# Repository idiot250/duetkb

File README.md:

# duetkb

**An open-source split stenography keyboard.**

duetkb is a DIY split stenography keyboard designed for fast, chord-based text input. It uses a compact two-piece layout, allowing both hands to operate independently while remaining connected to a single host computer.

i built this project for the idea of making dedicated stenographic hardware accessible, affordable, and customizable.

The first hardware revision is currently being designed. PCB design and firmware development are ongoing.

## Features

- Split keyboard architecture with independent left and right halves.
- 23-key stenographic layout.
- Wired USB-C connection to the host computer.
- Inter-half communication through a physical cable.
- ESP32-based hardware architecture.
- Designed for integration with [Plover](https://www.openstenoproject.org/plover/).
- Open-source hardware and firmware.

## Hardware

the keyboard is designed around two separate PCBs, one for each hand. it uses a row-and-column switch matrix with individual diodes to support simultaneous key presses and prevent unwanted electrical interactions.

| component | function |
|---|---|
| Microcontroller | ESP32 |
| Key switches | Mechanical switches |
| Diodes | Individual switch-matrix diodes |
| Host connection | USB-C |
| Inter-half connection | Wired |
| Layout | 23-key stenographic |

## repo structure

```text
duetkb/
├── hardware/
│   ├── left/
│   │   └── KiCad project files
│   └── right/
│       └── KiCad project files
├── firmware/
│   └── ESP-IDF project
├── JOURNAL.md
└── README.md
```

*Directory structure may change as development progresses.*

## Firmware

Firmware is being developed using **ESP-IDF**.

The intended firmware will handle:

- Switch matrix scanning.
- Simultaneous keypress detection.
- Communication between keyboard halves.
- Stenographic chord processing.
- USB HID output for compatibility with host computers and Plover.

## Software Compatibility

duetkb is intended to work with [Plover](https://www.openstenoproject.org/plover/), an open-source stenography engine.

The eventual goal is to translate simultaneous key combinations into stenographic input that Plover can interpret using a supported stenography dictionary and theory.

## Development

The hardware is designed in [KiCad](https://www.kicad.org/), while firmware development uses the ESP-IDF framework.

To work on the firmware, install ESP-IDF and its required toolchain.

```bash
git clone https://github.com/kurone741/duetkb.git
cd duetkb
```

Firmware build and flashing instructions will be added once the initial firmware implementation is ready.

## Roadmap

- [x] Establish project architecture.
- [x] Select initial hardware components.
- [x] Design left and right schematics.
- [x] Assign PCB footprints.
- [ ] Complete PCB component placement.
- [ ] Route both PCBs.
- [ ] Run PCB design-rule checks.
- [ ] Generate manufacturing files.
- [ ] Assemble hardware.
- [ ] Implement switch matrix scanning.
- [ ] Implement inter-half communication.
- [ ] Implement stenographic input processing.
- [ ] Test Plover compatibility.

## License

Licensing information will be added before the first public hardware and firmware release.

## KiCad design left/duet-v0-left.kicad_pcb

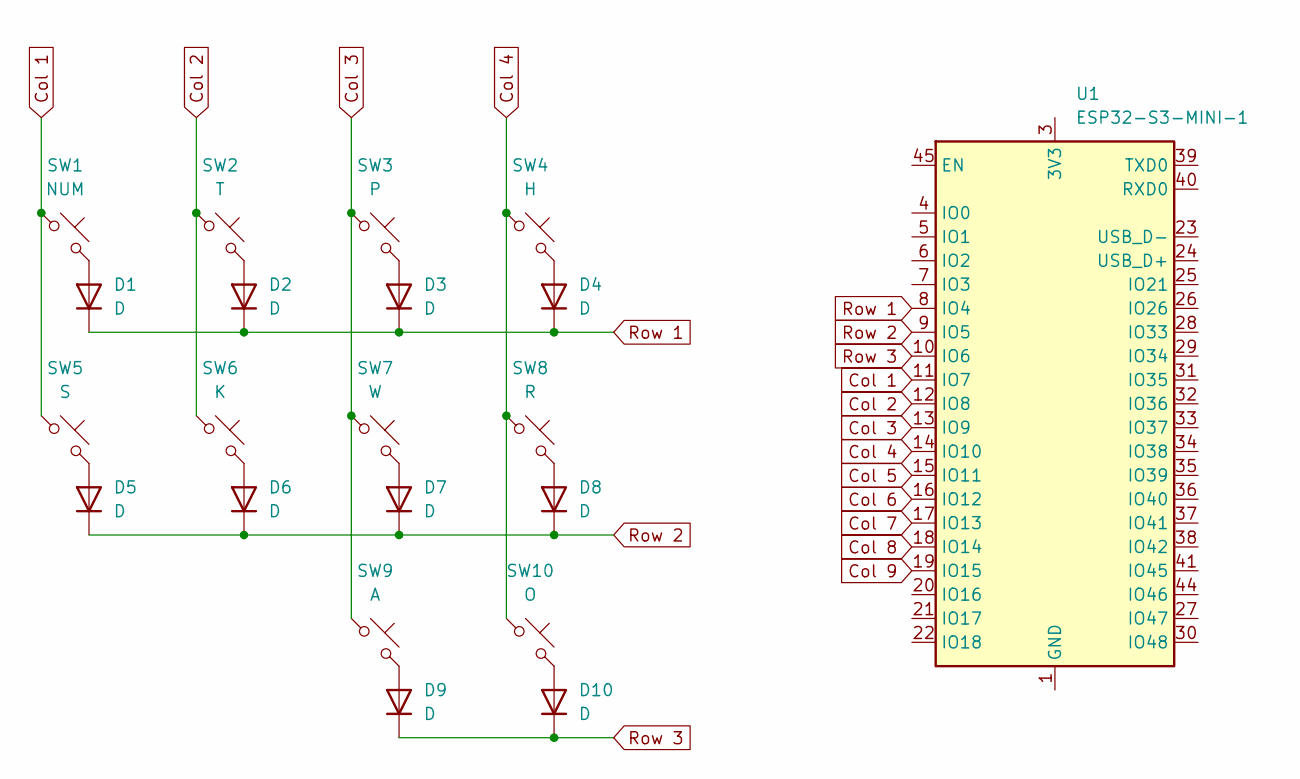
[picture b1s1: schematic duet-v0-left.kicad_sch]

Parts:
D1, D2, D3, D4, D5, D6, D7, D8, D9, D10: D; D_SOD-123
SW1: NUM; SW_Cherry_MX_1.00u_PCB
SW2: T; SW_Cherry_MX_1.00u_PCB
SW3: P; SW_Cherry_MX_1.00u_PCB
SW4: H; SW_Cherry_MX_1.00u_PCB
SW5: S; SW_Cherry_MX_1.00u_PCB
SW6: K; SW_Cherry_MX_1.00u_PCB
SW7: W; SW_Cherry_MX_1.00u_PCB
SW8: R; SW_Cherry_MX_1.00u_PCB
SW9: A; SW_Cherry_MX_1.00u_PCB
SW10: O; SW_Cherry_MX_1.00u_PCB
U1: ESP32-S3-MINI-1; ESP32-S2-MINI-1

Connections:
Col 1: SW1.1, SW5.1, U1.11 (IO7)
Col 2: SW2.1, SW6.1, U1.12 (IO8)
Col 3: SW3.1, SW7.1, SW9.1, U1.13 (IO9)
Col 4: SW4.1, SW8.1, SW10.1, U1.14 (IO10)
Col 5: U1.15 (IO11)
Col 6: U1.16 (IO12)
Col 7: U1.17 (IO13)
Col 8: U1.18 (IO14)
Col 9: U1.19 (IO15)
unnamed: D1.2 (A), SW1.2
unnamed: D2.2 (A), SW2.2
unnamed: D3.2 (A), SW3.2
unnamed: D4.2 (A), SW4.2
unnamed: D5.2 (A), SW5.2
unnamed: D6.2 (A), SW6.2
unnamed: D7.2 (A), SW7.2
unnamed: D8.2 (A), SW8.2
unnamed: D9.2 (A), SW9.2
unnamed: D10.2 (A), SW10.2
unnamed: U1.1 (GND), U1.2 (GND), U1.42 (GND), U1.43 (GND), U1.46 (GND), U1.47 (GND), U1.48 (GND), U1.49 (GND), U1.50 (GND), U1.51 (GND), U1.52 (GND), U1.53 (GND), U1.54 (GND), U1.55 (GND), U1.56 (GND), U1.57 (GND), U1.58 (GND), U1.59 (GND), U1.60 (GND), U1.61 (GND), U1.62 (GND), U1.63 (GND), U1.64 (GND), U1.65 (GND)
Row 1: D1.1 (K), D2.1 (K), D3.1 (K), D4.1 (K), U1.8 (IO4)
Row 2: D5.1 (K), D6.1 (K), D7.1 (K), D8.1 (K), U1.9 (IO5)
Row 3: D9.1 (K), D10.1 (K), U1.10 (IO6)

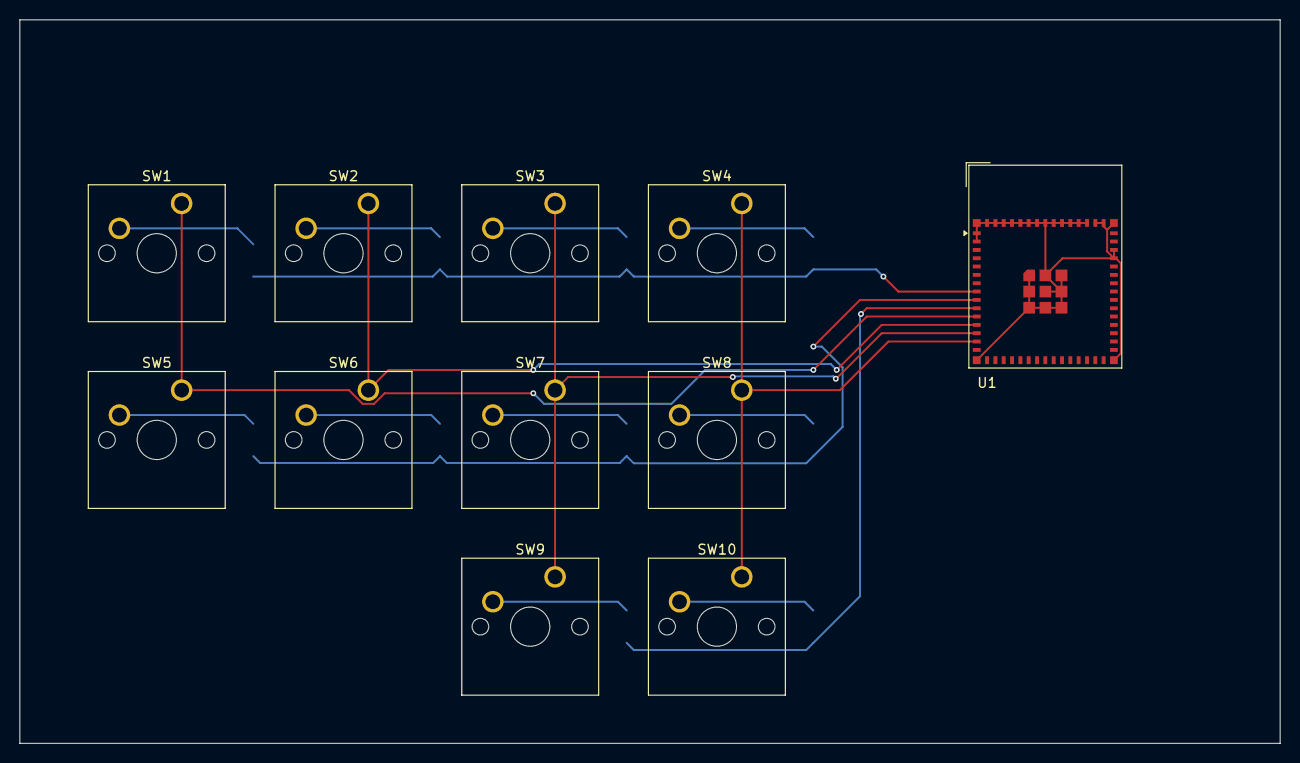
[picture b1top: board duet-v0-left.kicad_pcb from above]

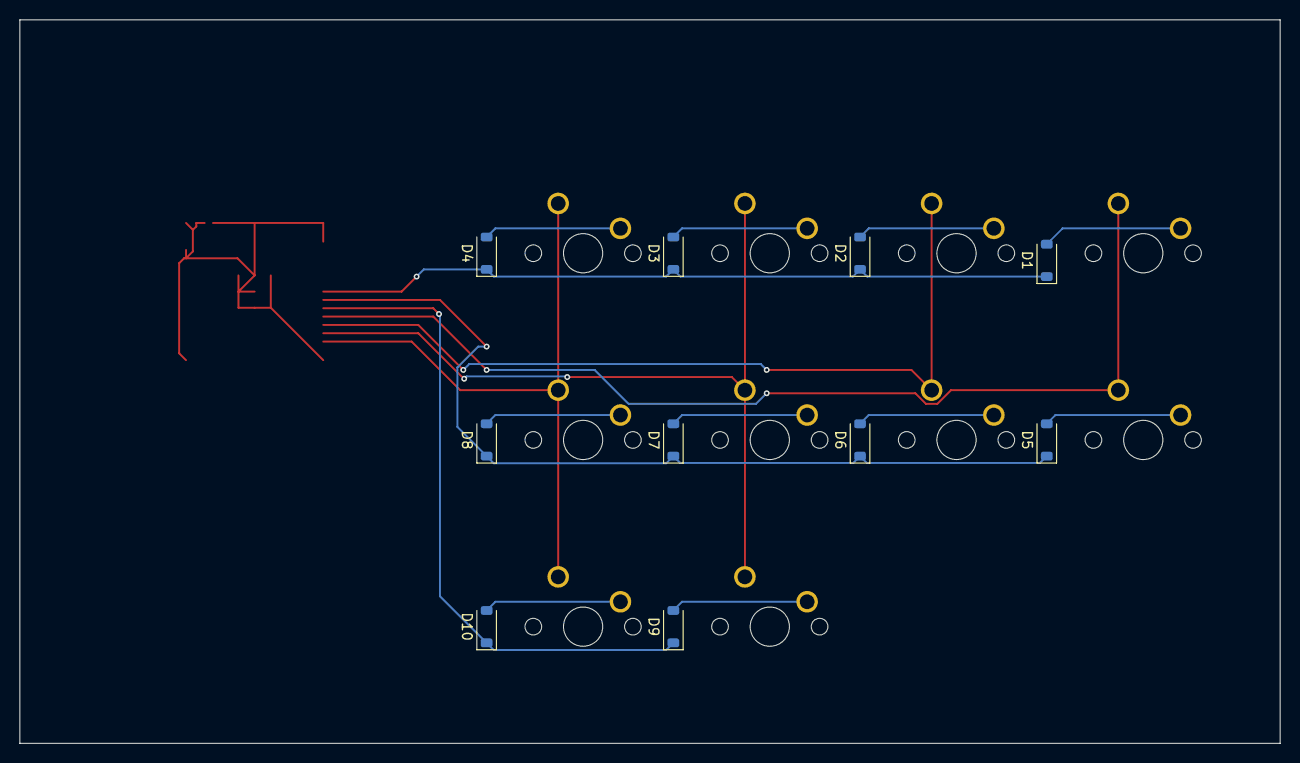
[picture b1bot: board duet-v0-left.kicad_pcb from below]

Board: 2 copper layers, 128.6 x 73.8 mm, 21 parts (10 on the bottom side), 18 nets.
